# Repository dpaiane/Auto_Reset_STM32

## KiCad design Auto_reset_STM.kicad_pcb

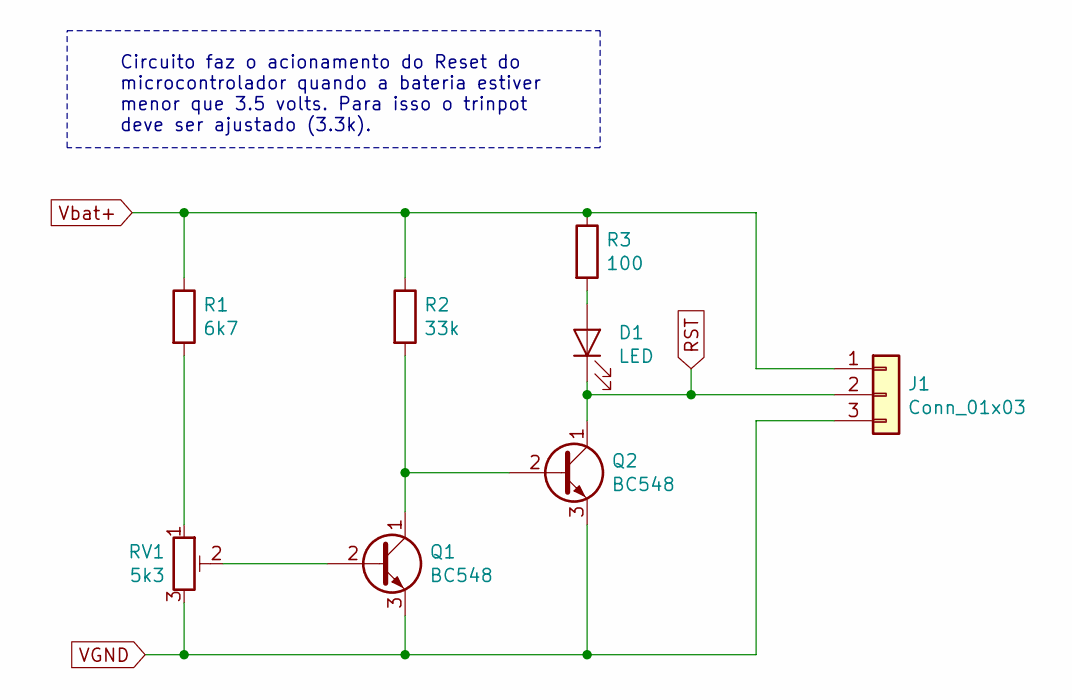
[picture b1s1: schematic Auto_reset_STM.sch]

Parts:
D1: LED; LED_D3.0mm
J1: Conn_01x03; PinHeader_1x03_P1.00mm_Vertical
Q1, Q2: BC548; TO-92_Inline
R1: 6k7; R_Axial_DIN0207_L6.3mm_D2.5mm_P7.62mm_Horizontal
R2: 33k; R_Axial_DIN0207_L6.3mm_D2.5mm_P7.62mm_Horizontal
R3: 100; R_Axial_DIN0207_L6.3mm_D2.5mm_P7.62mm_Horizontal
RV1: 5k3; Potentiometer_Bourns_3299W_Vertical

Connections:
unnamed: D1.2 (A), R3.2
unnamed: Q1.1 (C), Q2.2 (B), R2.2
unnamed: Q1.2 (B), RV1.2
unnamed: R1.2, RV1.1
RST: D1.1 (K), J1.2, Q2.1 (C)
VGND: J1.3, Q1.3 (E), Q2.3 (E), RV1.3
Vbat+: J1.1, R1.1, R2.1, R3.1

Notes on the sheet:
Circuito faz o acionamento do Reset do microcontrolador quando a bateria estiver menor que 3.5 volts. Para isso o trinpot deve ser ajustado (3.3k).

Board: 2 copper layers, 8 parts (0 on the bottom side), 7 nets, no tracks yet.
